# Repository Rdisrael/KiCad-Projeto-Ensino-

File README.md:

# Projeto:Simuladores e Experimentos Práticos voltados à Eletrônica Analógica.
## Apostila Prática Software KiCad 7

Projeto de ensino realizado com o objetivo de contribuir na realização de projetos de placas de circuito impresso.
Os arquivos dos cinco projetos devem ser abertos no kicad 7.
É sugerido que use a apostila teorica juntamente com a apostila prática para uma maior compreensão.
Essa não é a versão final da apostila serão criados repositórios para as etapas de confecção.

Teaching project carried out with the aim of contributing in the realization of printed circuit board projects.
The files for the five projects must be opened in Kicad 7.
It is suggested that you use the theoretical booklet together with the practical booklet for greater understanding. This is not the final version of the booklet will be created for the preparation steps.

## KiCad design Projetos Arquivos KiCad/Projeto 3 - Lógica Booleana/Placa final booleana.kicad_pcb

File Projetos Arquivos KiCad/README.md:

É aconselhavel que faça o download de toda a pasta para que todos os arquivos estejam anexados ao projeto. 
Provavelmente será necessário anexar as footprins e os modelos 3D caso eles não apareçam na visão 3D.
Fique a vontade para editar os projetos bem como quiser.

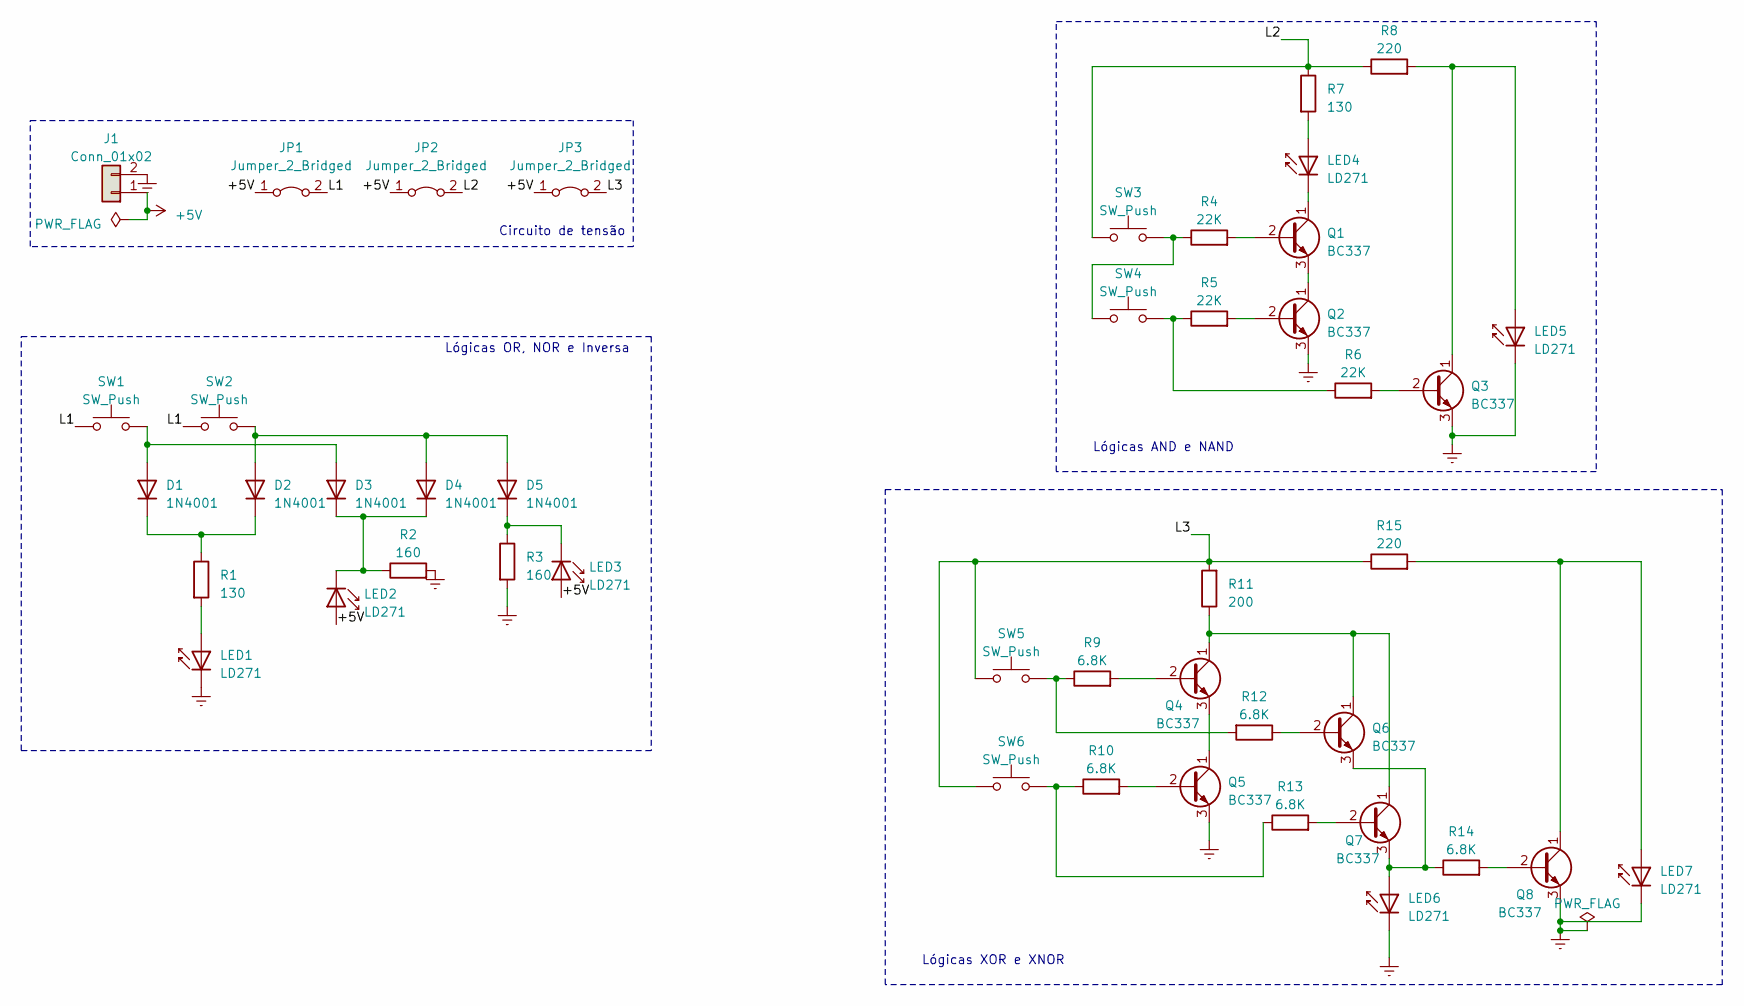
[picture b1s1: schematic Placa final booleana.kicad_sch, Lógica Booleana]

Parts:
D1, D2, D3, D4, D5: 1N4001; D_DO-41_SOD81_P10.16mm_Horizontal
J1: Conn_01x02; PinSocket_2x01_P2.54mm_Vertical
JP1, JP2, JP3: Jumper_2_Bridged; PinHeader_1x02_P2.54mm_Vertical
LED1, LED2, LED3, LED4, LED5, LED6, LED7: LD271; LED_D5.0mm_IRGrey
Q1, Q2, Q3, Q4, Q5, Q6, Q7, Q8: BC337; TO-92_Wide
R1, R7: 130; R_Axial_DIN0207_L6.3mm_D2.5mm_P10.16mm_Horizontal
R2, R3: 160; R_Axial_DIN0207_L6.3mm_D2.5mm_P10.16mm_Horizontal
R4, R5, R6: 22K; R_Axial_DIN0207_L6.3mm_D2.5mm_P10.16mm_Horizontal
R8, R15: 220; R_Axial_DIN0207_L6.3mm_D2.5mm_P10.16mm_Horizontal
R9, R10, R12, R13, R14: 6.8K; R_Axial_DIN0207_L6.3mm_D2.5mm_P10.16mm_Horizontal
R11: 200; R_Axial_DIN0207_L6.3mm_D2.5mm_P10.16mm_Horizontal
SW1, SW2, SW3, SW4, SW5, SW6: SW_Push; SW_PUSH_6mm

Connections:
+5V: J1.1, JP1.1 (A), JP2.1 (A), JP3.1 (A), LED2.2 (A), LED3.2 (A)
/L1: JP1.2 (B), SW1.1, SW2.1
/L2: JP2.2 (B), R7.1, R8.1, SW3.1
/L3: JP3.2 (B), R11.2, R15.1, SW5.1, SW6.1
Earth: J1.2, LED1.1 (K), LED5.1 (K), LED6.1 (K), LED7.1 (K), Q2.3 (E), Q3.3 (E), Q5.3 (E), Q8.3 (E), R2.2, R3.2
unnamed: D1.2 (A), D3.2 (A), SW1.2
unnamed: D1.1 (K), D2.1 (K), R1.1
unnamed: D2.2 (A), D4.2 (A), D5.2 (A), SW2.2
unnamed: D3.1 (K), D4.1 (K), LED2.1 (K), R2.1
unnamed: D5.1 (K), LED3.1 (K), R3.1
unnamed: LED1.2 (A), R1.2
unnamed: LED4.2 (A), R7.2
unnamed: LED4.1 (K), Q1.1 (C)
unnamed: LED5.2 (A), Q3.1 (C), R8.2
unnamed: LED6.2 (A), Q6.3 (E), Q7.3 (E), R14.1
unnamed: LED7.2 (A), Q8.1 (C), R15.2
unnamed: Q1.2 (B), R4.2
unnamed: Q1.3 (E), Q2.1 (C)
unnamed: Q2.2 (B), R5.2
unnamed: Q3.2 (B), R6.2
unnamed: Q4.2 (B), R9.2
unnamed: Q4.1 (C), Q6.1 (C), Q7.1 (C), R11.1
unnamed: Q4.3 (E), Q5.1 (C)
unnamed: Q5.2 (B), R10.2
unnamed: Q6.2 (B), R12.1
unnamed: Q7.2 (B), R13.2
unnamed: Q8.2 (B), R14.2
unnamed: R4.1, SW3.2, SW4.1
unnamed: R5.1, R6.1, SW4.2
unnamed: R10.1, R13.1, SW6.2
unnamed: R9.1, R12.2, SW5.2

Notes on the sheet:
Lógicas OR, NOR e Inversa
Lógicas AND e NAND
Circuito de tensão
Lógicas XOR e XNOR

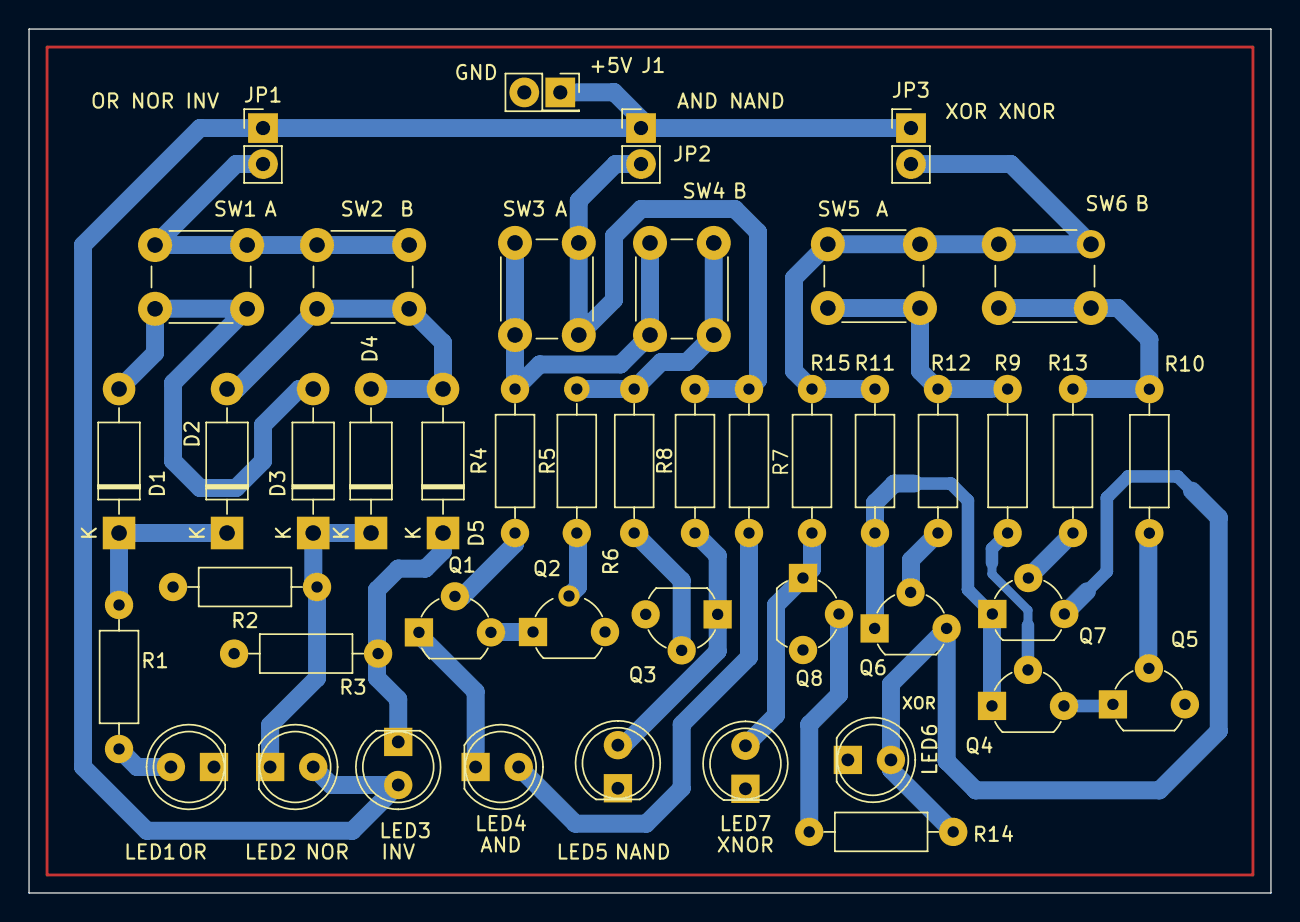
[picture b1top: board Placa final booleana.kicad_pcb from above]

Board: 2 copper layers, 87.6 x 61.0 mm, 45 parts (0 on the bottom side), 31 nets.

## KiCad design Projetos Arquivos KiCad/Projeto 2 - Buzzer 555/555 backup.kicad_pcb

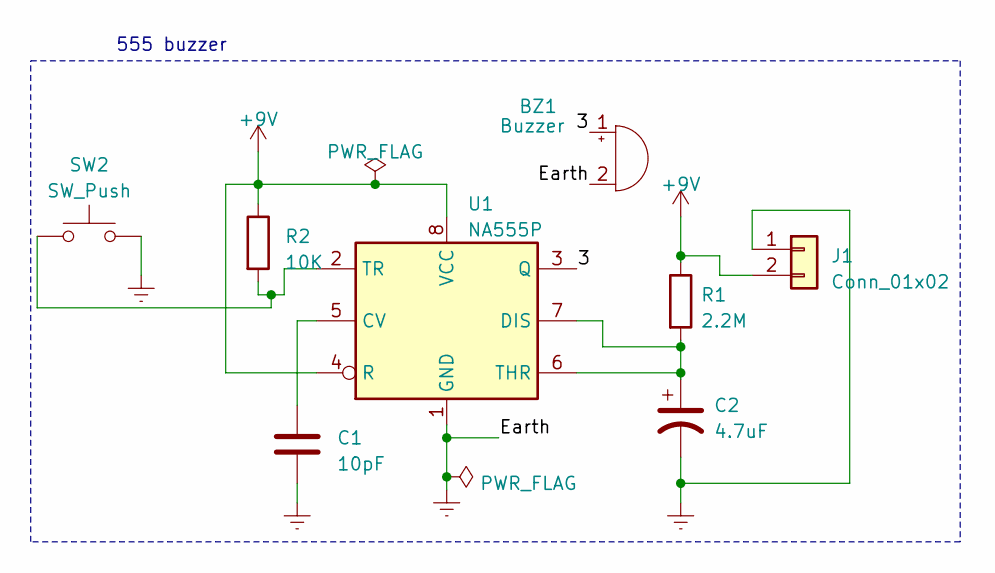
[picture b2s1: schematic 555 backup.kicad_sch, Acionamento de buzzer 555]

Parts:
BZ1: Buzzer; Buzzer_12x9.5RM7.6
C1: 10pF; C_Disc_D3.0mm_W2.0mm_P2.50mm
C2: 4.7uF; CP_Radial_D5.0mm_P2.50mm
J1: Conn_01x02; PinSocket_2x01_P2.00mm_Vertical
R1: 2.2M; R_Axial_DIN0207_L6.3mm_D2.5mm_P10.16mm_Horizontal
R2: 10K; R_Axial_DIN0207_L6.3mm_D2.5mm_P10.16mm_Horizontal
SW2: SW_Push; SW_PUSH_6mm
U1: NA555P; DIP-8_W7.62mm

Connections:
+9V: J1.2, R1.1, R2.1, U1.4 (R), U1.8 (VCC)
/3: BZ1.1 (-), U1.3 (Q)
Earth: BZ1.2 (+), C1.2, C2.2, J1.1, SW2.2, U1.1 (GND)
unnamed: C1.1, U1.5 (CV)
unnamed: C2.1, R1.2, U1.6 (THR), U1.7 (DIS)
unnamed: R2.2, SW2.1, U1.2 (TR)

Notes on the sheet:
555 buzzer

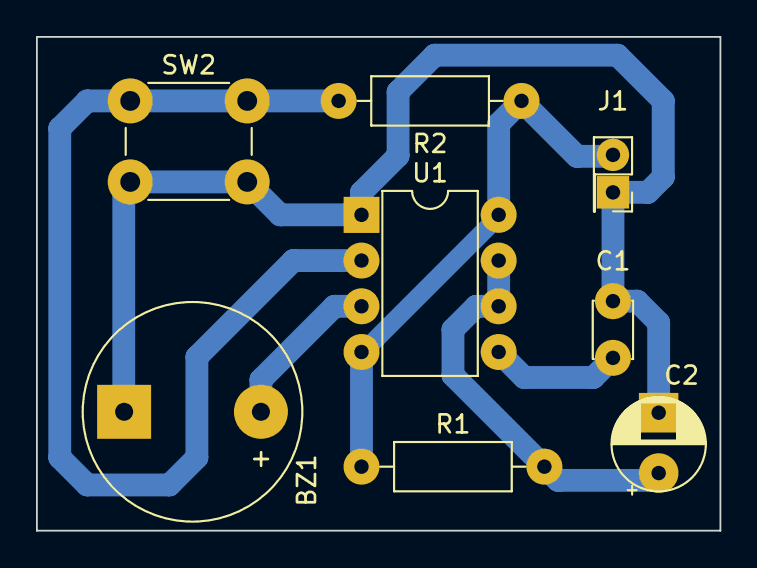
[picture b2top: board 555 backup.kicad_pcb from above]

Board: 2 copper layers, 38.0 x 27.4 mm, 8 parts (0 on the bottom side), 6 nets.

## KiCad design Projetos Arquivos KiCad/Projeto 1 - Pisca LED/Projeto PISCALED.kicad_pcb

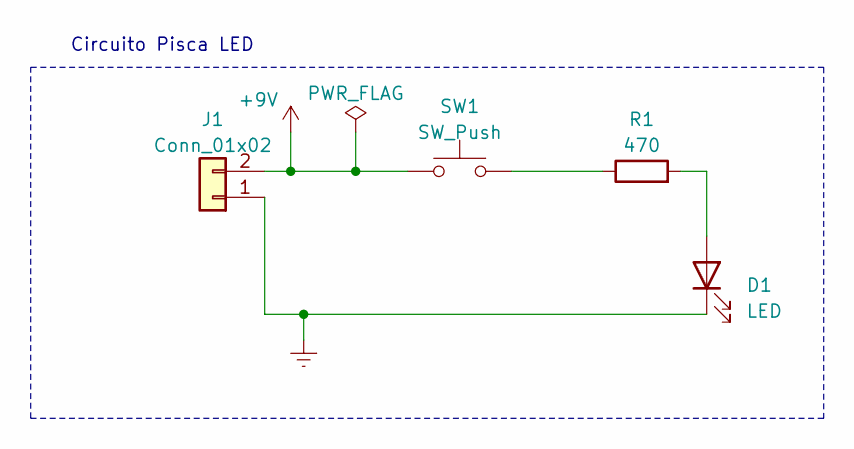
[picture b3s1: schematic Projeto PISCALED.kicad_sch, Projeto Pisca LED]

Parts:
D1: LED; LED_D5.0mm
J1: Conn_01x02; PinSocket_1x02_P2.54mm_Vertical
R1: 470; R_Axial_DIN0207_L6.3mm_D2.5mm_P10.16mm_Horizontal
SW1: SW_Push; SW_PUSH_6mm

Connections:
+9V: J1.2, SW1.1
Earth: D1.1 (K), J1.1
unnamed: D1.2 (A), R1.2
unnamed: R1.1, SW1.2

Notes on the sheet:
Circuito Pisca LED

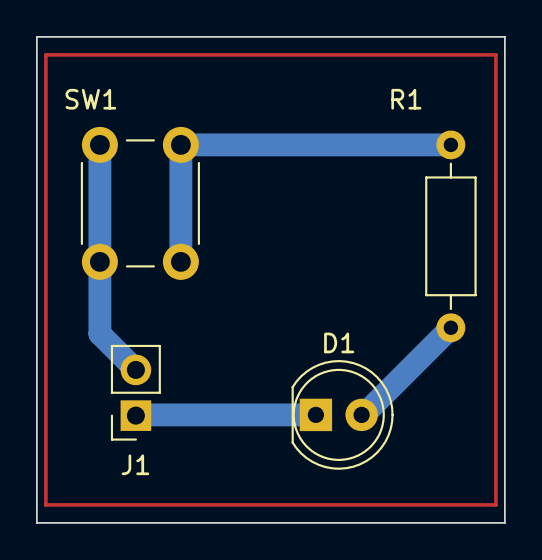
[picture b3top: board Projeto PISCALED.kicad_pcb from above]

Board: 2 copper layers, 26.0 x 27.0 mm, 4 parts (0 on the bottom side), 4 nets.

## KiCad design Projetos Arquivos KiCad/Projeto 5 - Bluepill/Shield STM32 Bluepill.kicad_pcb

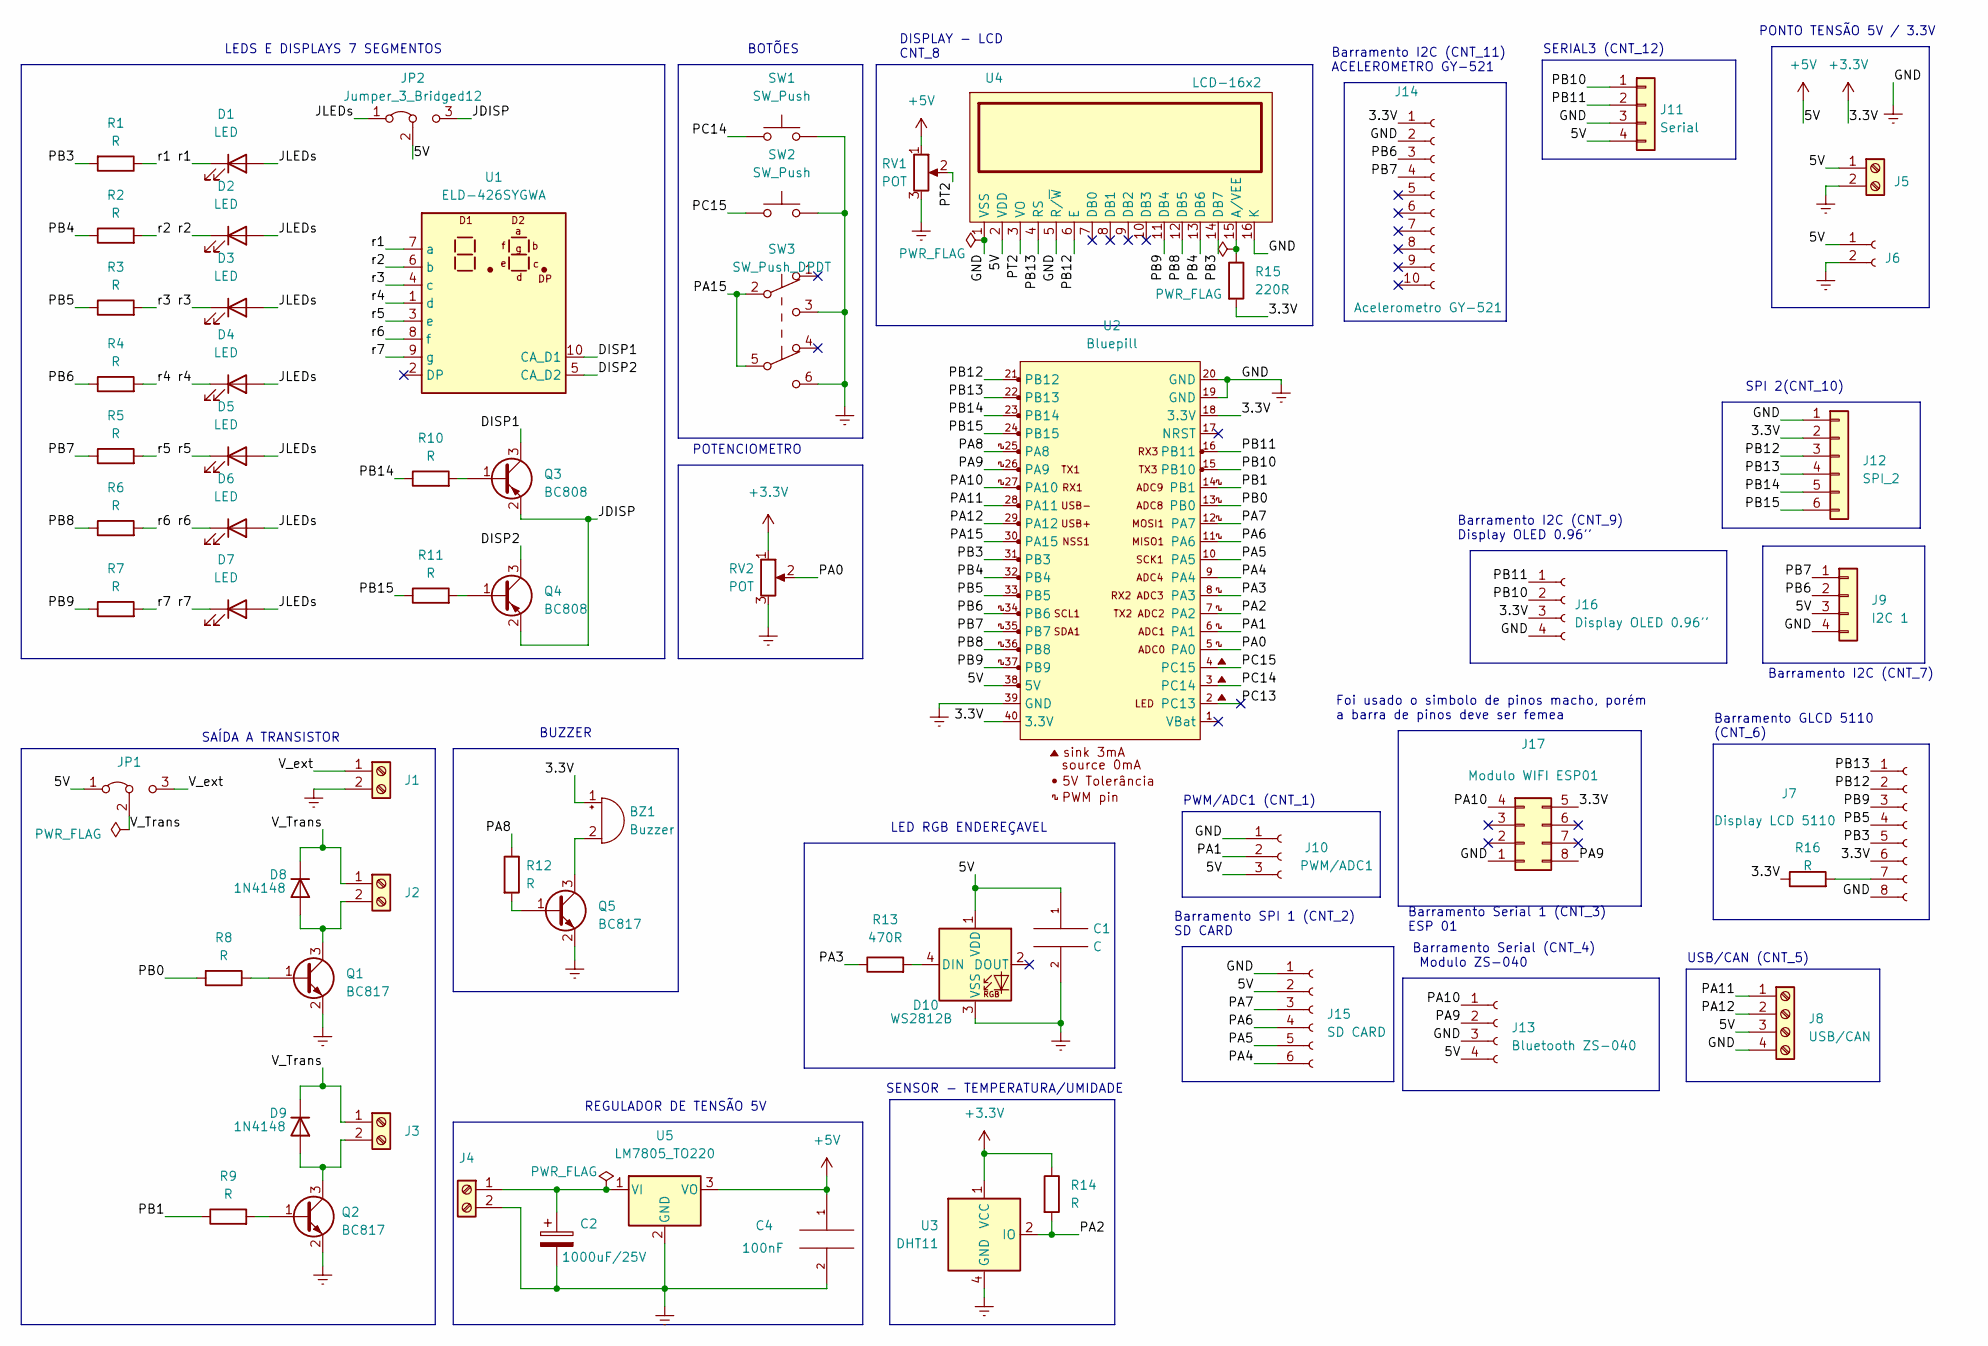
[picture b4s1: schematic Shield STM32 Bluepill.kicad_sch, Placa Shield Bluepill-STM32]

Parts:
BZ1: Buzzer; Buzzer_12x9.5RM7.6
C1: C; C_1206_3216Metric
C2: 1000uF/25V; CP_Elec_10x10
C4: 100nF; C_1206_3216Metric
D1, D2, D3, D4, D5, D6, D7: LED; LED_1206_3216Metric
D8, D9: 1N4148; D_1206_3216Metric
D10: WS2812B; LED_WS2812B_PLCC4_5.0x5.0mm_P3.2mm
J1, J2, J3, J4, J5: Screw_Terminal_01x02; TerminalBlock_Phoenix_MKDS-1,5-2-5.08_1x02_P5.08mm_Horizont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
J6: Conn_01x02_Female; PinSocket_1x02_P2.54mm_Vertical
J7: Display LCD 5110; PinSocket_1x08_P2.54mm_Vertical
J8: USB/CAN; TerminalBlock_Phoenix_MKDS-1,5-4-5.08_1x04_P5.08mm_Horizont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
J9: I2C 1; Molex_KK-254_AE-6410-04A_1x04_P2.54mm_Vertical
J10: PWM/ADC1; PinSocket_1x03_P2.54mm_Vertical
J11: Serial; Molex_KK-254_AE-6410-04A_1x04_P2.54mm_Vertical
J12: SPI_2; Molex_KK-254_AE-6410-06A_1x06_P2.54mm_Vertical
J13: Bluetooth ZS-040; PinSocket_1x04_P2.54mm_Vertical
J14: Acelerometro GY-521; PinSocket_1x10_P2.54mm_Vertical
J15: SD CARD; PinSocket_1x06_P2.54mm_Vertical
J16: Display OLED 0.96''; PinSocket_1x04_P2.54mm_Vertical
J17: Modulo WIFI ESP01; PinSocket_2x04_P2.54mm_Vertical
JP1, JP2: Jumper_3_Bridged12; PinHeader_1x03_P2.54mm_Vertical
Q1, Q2, Q5: BC817; SOT-23
Q3, Q4: BC808; SOT-23
R1, R2, R3, R4, R5, R6, R7, R8, R9, R10, R11, R12, R14, R16: R; R_1206_3216Metric
R13: 470R; R_1206_3216Metric
R15: 220R; R_1206_3216Metric
RV1: POT; Potentiometer_Bourns_3006P_Horizontal
RV2: POT; Potentiometer_Bourns_3339P_Vertical
SW1, SW2: SW_Push; SW_PUSH_6mm_H7.3mm
SW3: SW_Push_DPDT; SW_TL2201EEYA
U1: ELD-426SYGWA; ELD_426XXXX
U2: Bluepill; YAAJ_BluePill_SWD_1
U3: DHT11; Aosong_DHT11_5.5x12.0_P2.54mm
U4: LCD-16x2; WC1602A
U5: LM7805_TO220; TO-220-3_Vertical

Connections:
+3V3: BZ1.1 (-), J7.6, J12.2, J14.1, J16.3, J17.5, R14.1, R15.2, R16.1, RV2.1, U2.18 (3.3V), U2.40 (3.3V), U3.1 (VCC)
+5V: C1.1, C4.1, D10.1 (VDD), J5.1, J6.1, J8.3, J9.3, J10.3, J11.4, J13.4, J15.2, JP1.1 (A), JP2.2 (C), RV1.1, U2.38 (5V), U4.2 (VDD), U5.3 (VO)
/DISP1: Q3.3 (C), U1.10 (CA_D1)
/DISP2: Q4.3 (C), U1.5 (CA_D2)
/JDISP: JP2.3 (B), Q3.2 (E), Q4.2 (E)
/JLEDs: D1.2 (A), D2.2 (A), D3.2 (A), D4.2 (A), D5.2 (A), D6.2 (A), D7.2 (A), JP2.1 (A)
/PA0: RV2.2, U2.5 (PA0)
/PA1: J10.2, U2.6 (PA1)
/PA2: R14.2, U2.7 (PA2), U3.2 (IO)
/PA3: R13.1, U2.8 (PA3)
/PA4: J15.6, U2.9 (PA4)
/PA5: J15.5, U2.10 (PA5)
/PA6: J15.4, U2.11 (PA6)
/PA7: J15.3, U2.12 (PA7)
/PA8: R12.1, U2.25 (PA8)
/PA9: J13.2, J17.8, U2.26 (PA9)
/PA10: J13.1, J17.4, U2.27 (PA10)
/PA11: J8.1, U2.28 (PA11)
/PA12: J8.2, U2.29 (PA12)
/PA15: SW3.2 (B), SW3.5 (B), U2.30 (PA15)
/PB0: R8.2, U2.13 (PB0)
/PB1: R9.1, U2.14 (PB1)
/PB3: J7.5, R1.2, U2.31 (PB3), U4.14 (DB7)
/PB4: R2.1, U2.32 (PB4), U4.13 (DB6)
/PB5: J7.4, R3.1, U2.33 (PB5)
/PB6: J9.2, J14.3, R4.1, U2.34 (PB6)
/PB7: J9.1, J14.4, R5.1, U2.35 (PB7)
/PB8: R6.1, U2.36 (PB8), U4.12 (DB5)
/PB9: J7.3, R7.1, U2.37 (PB9), U4.11 (DB4)
/PB10: J11.1, J16.2, U2.15 (PB10)
/PB11: J11.2, J16.1, U2.16 (PB11)
/PB12: J7.2, J12.3, U2.21 (PB12), U4.6 (E)
/PB13: J7.1, J12.4, U2.22 (PB13), U4.4 (RS)
/PB14: J12.5, R10.1, U2.23 (PB14)
/PB15: J12.6, R11.1, U2.24 (PB15)
/PC13: U2.2 (PC13)
/PC14: SW1.1, U2.3 (PC14)
/PC15: SW2.1, U2.4 (PC15)
/PT2: RV1.2, U4.3 (VO)
/V_Trans: D8.1 (K), D9.1 (K), J2.1, J3.1, JP1.2 (C)
/V_ext: J1.1, JP1.3 (B)
/r1: D1.1 (K), R1.1, U1.7 (a)
/r2: D2.1 (K), R2.2, U1.6 (b)
/r3: D3.1 (K), R3.2, U1.4 (c)
/r4: D4.1 (K), R4.2, U1.1 (d)
/r5: D5.1 (K), R5.2, U1.3 (e)
/r6: D6.1 (K), R6.2, U1.8 (f)
/r7: D7.1 (K), R7.2, U1.9 (g)
Earth: C1.2, C2.2, C4.2, D10.3 (VSS), J1.2, J4.2, J5.2, J6.2, J7.8, J8.4, J9.4, J10.1, J11.3, J12.1, J13.3, J14.2, J15.1, J16.4, J17.1, Q1.2 (E), Q2.2 (E), Q5.2 (E), RV1.3, RV2.3, SW1.2, SW2.2, SW3.3 (C), SW3.6 (C), U2.19 (GND), U2.20 (GND), U2.39 (GND), U3.4 (GND), U4.1 (VSS), U4.5 (R/~W), U4.16 (K), U5.2 (GND)
unnamed: R15.1, U4.15 (A/VEE)
unnamed: C2.1, J4.1, U5.1 (VI)
unnamed: BZ1.2 (+), Q5.3 (C)
unnamed: D8.2 (A), J2.2, Q1.3 (C)
unnamed: D9.2 (A), J3.2, Q2.3 (C)
unnamed: D10.4 (DIN), R13.2
unnamed: J7.7, R16.2
unnamed: Q1.1 (B), R8.1
unnamed: Q2.1 (B), R9.2
unnamed: Q3.1 (B), R10.2
unnamed: Q4.1 (B), R11.2
unnamed: Q5.1 (B), R12.2

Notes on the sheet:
SAÍDA A TRANSISTOR
DISPLAY - LCD CNT_8
SENSOR - TEMPERATURA/UMIDADE
LEDS E DISPLAYS 7 SEGMENTOS
REGULADOR DE TENSÃO 5V
Barramento Serial (CNT_4) Modulo ZS-040
Barramento GLCD 5110 (CNT_6)
BUZZER
POTENCIOMETRO
PWM/ADC1 (CNT_1)
SERIAL3 (CNT_12)
Barramento I2C (CNT_9) Display OLED 0.96''
SPI 2(CNT_10)
Barramento Serial 1 (CNT_3) ESP 01
Barramento SPI 1 (CNT_2) SD CARD
Foi usado o simbolo de pinos macho, porém a barra de pinos deve ser femea
Barramento I2C (CNT_11) ACELEROMETRO GY-521
Barramento I2C (CNT_7)
LED RGB ENDEREÇAVEL
USB/CAN (CNT_5)
BOTÕES
PONTO TENSÃO 5V / 3.3V

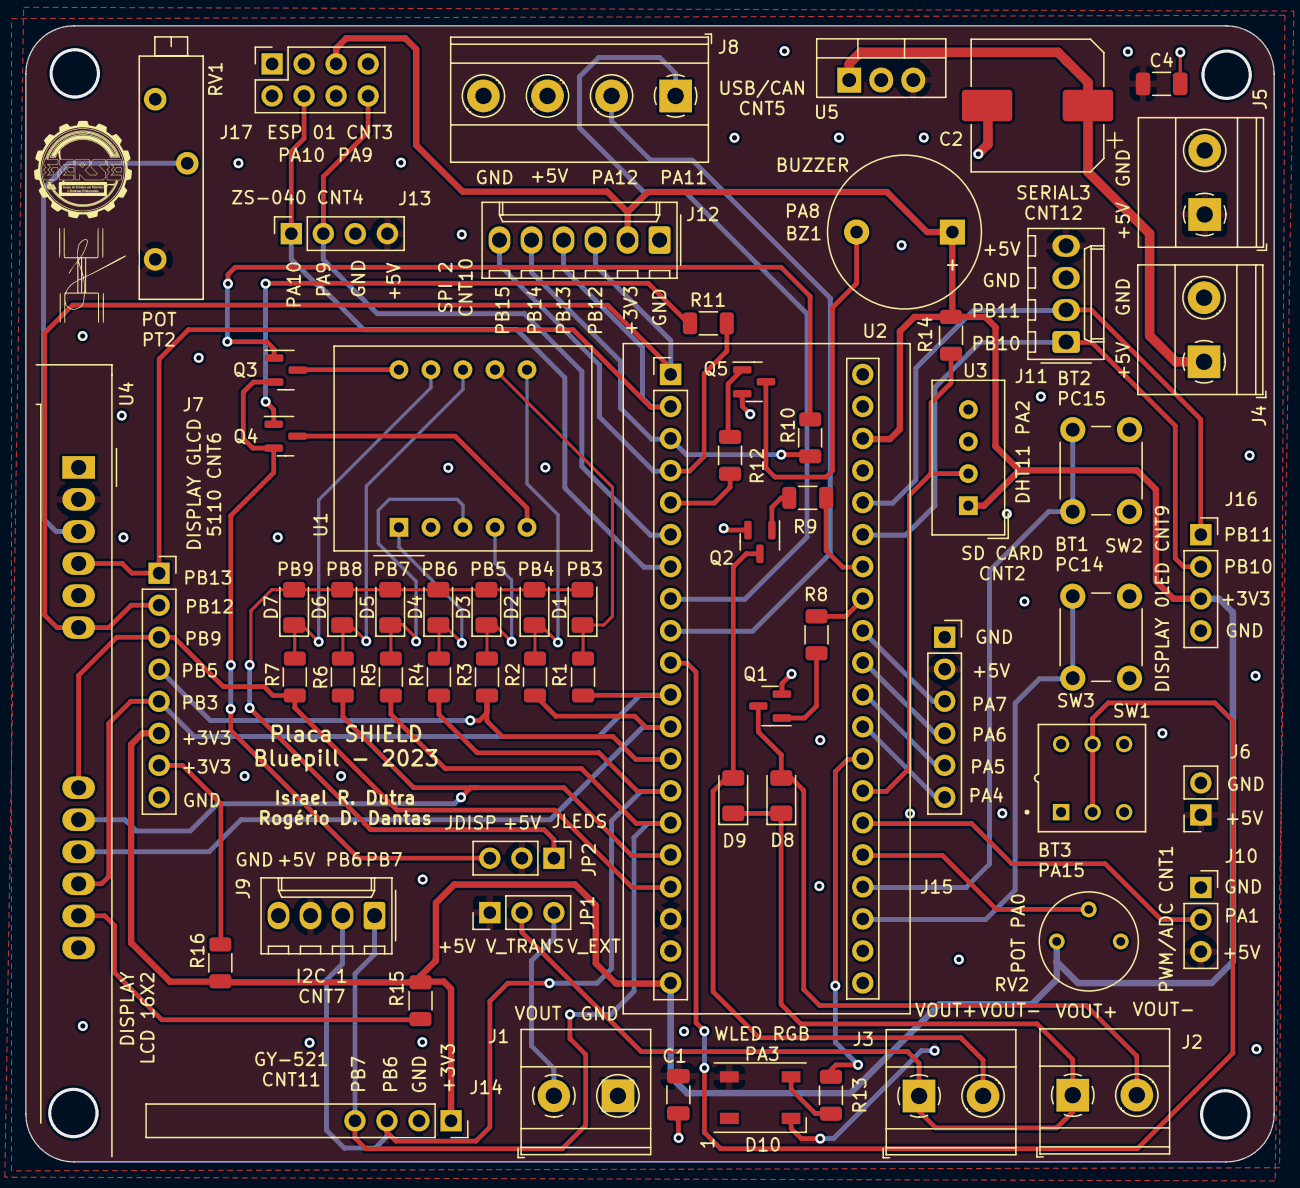
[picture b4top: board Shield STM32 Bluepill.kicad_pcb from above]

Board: 2 copper layers, 99.0 x 90.1 mm, 64 parts (0 on the bottom side), 60 nets.

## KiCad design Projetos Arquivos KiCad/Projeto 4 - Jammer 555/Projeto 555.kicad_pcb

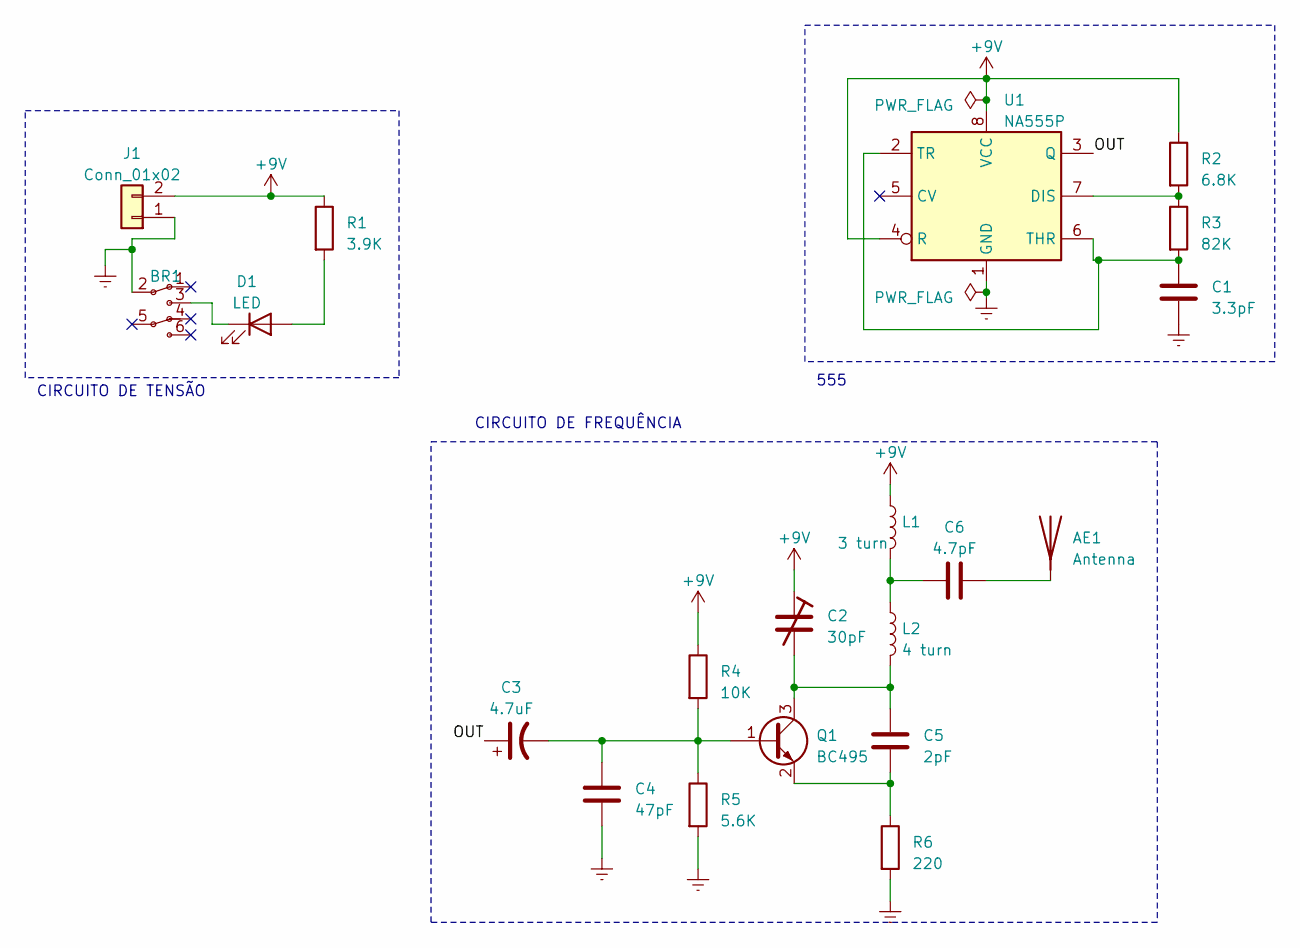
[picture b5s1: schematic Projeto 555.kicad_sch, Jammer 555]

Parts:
AE1: Antenna; Pin_D1.0mm_L10.0mm_LooseFit
BR1: Botão com retenção
C1: 3.3pF; C_Disc_D5.0mm_W2.5mm_P2.50mm
C2: 30pF; CP_Radial_Tantal_D5.5mm_P5.00mm
C3: 4.7uF; CP_Radial_D4.0mm_P2.00mm
C4: 47pF; C_Disc_D5.0mm_W2.5mm_P2.50mm
C5: 2pF; C_Disc_D5.0mm_W2.5mm_P2.50mm
C6: 4.7pF; C_Disc_D5.0mm_W2.5mm_P2.50mm
D1: LED; LED_D5.0mm_IRBlack
J1: Conn_01x02; PinSocket_2x01_P2.54mm_Vertical
L1: 3 turn; L_Axial_L5.3mm_D2.2mm_P10.16mm_Horizontal_Vishay_IM-1
L2: 4 turn; L_Axial_L5.3mm_D2.2mm_P10.16mm_Horizontal_Vishay_IM-1
Q1: BC495; TO-92_Wide
R1: 3.9K; R_Axial_DIN0207_L6.3mm_D2.5mm_P10.16mm_Horizontal
R2: 6.8K; R_Axial_DIN0207_L6.3mm_D2.5mm_P10.16mm_Horizontal
R3: 82K; R_Axial_DIN0207_L6.3mm_D2.5mm_P10.16mm_Horizontal
R4: 10K; R_Axial_DIN0207_L6.3mm_D2.5mm_P10.16mm_Horizontal
R5: 5.6K; R_Axial_DIN0207_L6.3mm_D2.5mm_P10.16mm_Horizontal
R6: 220; R_Axial_DIN0207_L6.3mm_D2.5mm_P10.16mm_Horizontal
U1: NA555P; DIP-8_W7.62mm

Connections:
+9V: C2.1, J1.2, L1.1, R1.1, R2.1, R4.1, U1.4 (R), U1.8 (VCC)
/OUT: C3.1, U1.3 (Q)
Earth: BR1.2, C1.2, C4.2, J1.1, R5.2, R6.2, U1.1 (GND)
unnamed: AE1.1 (A), C6.2
unnamed: C6.1, L1.2, L2.1
unnamed: D1.2 (A), R1.2
unnamed: BR1.3, D1.1 (K)
unnamed: C3.2, C4.1, Q1.1 (B), R4.2, R5.1
unnamed: C2.2, C5.1, L2.2, Q1.3 (C)
unnamed: C5.2, Q1.2 (E), R6.1
unnamed: R2.2, R3.1, U1.7 (DIS)
unnamed: C1.1, R3.2, U1.2 (TR), U1.6 (THR)

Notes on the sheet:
CIRCUITO DE FREQUÊNCIA
555
CIRCUITO DE TENSÃO

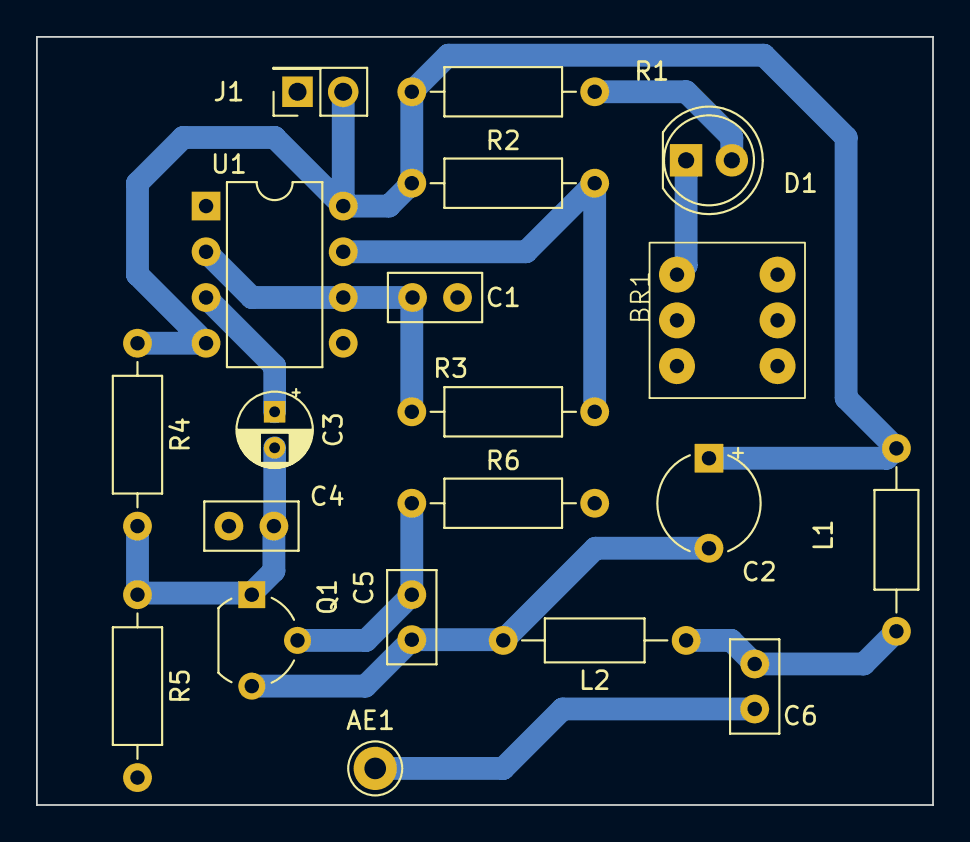
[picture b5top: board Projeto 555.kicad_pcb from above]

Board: 2 copper layers, 49.8 x 42.7 mm, 20 parts (0 on the bottom side), 12 nets.

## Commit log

2023-12-28 Arquivos do Kicad
2023-12-28 README.md
